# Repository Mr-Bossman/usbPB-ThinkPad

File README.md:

# usbPB-ThinkPad
A usb PD converter for lenovo slim tip chargers

Writen in C, small ram and code space.

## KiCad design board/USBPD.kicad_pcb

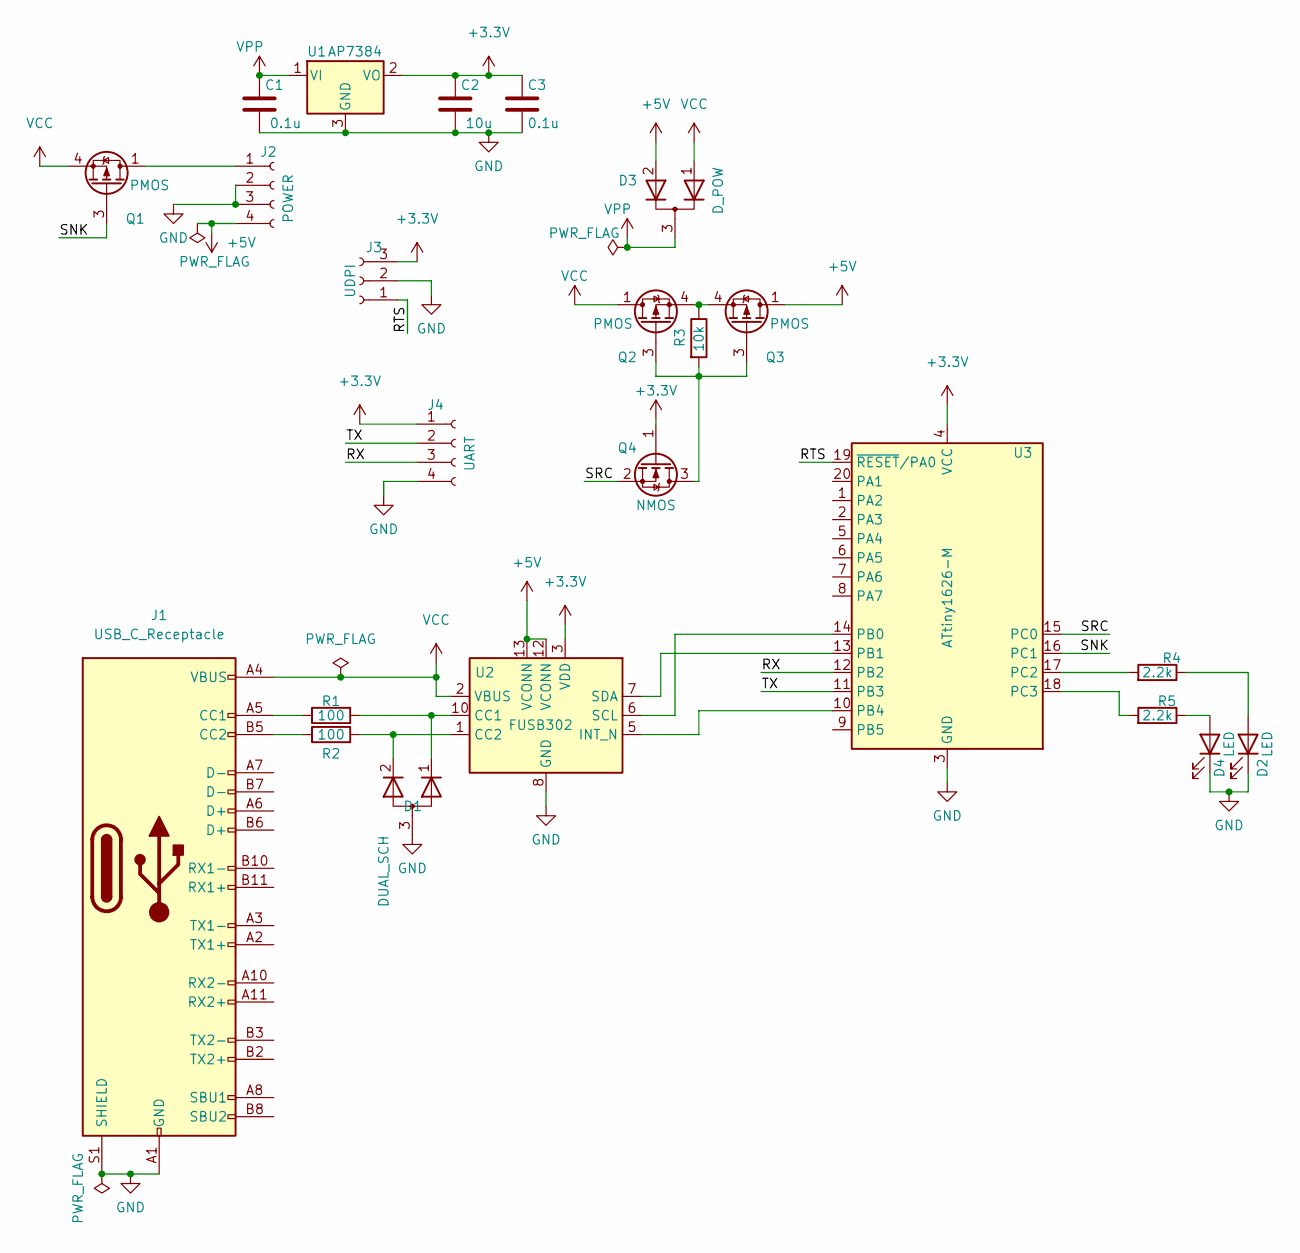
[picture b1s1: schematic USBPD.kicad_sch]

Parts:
C1, C3: 0.1u; C_0603_1608Metric
C2: 10u; C_0603_1608Metric
D1: DUAL_SCH; SOT-23
D2, D4: LED; LED_0603_1608Metric
D3: D_POW; SOT-23
J1: USB_C_Receptacle; USB_C_Receptacle_GCT_USB4085
J2: POWER; PinHeader_1x04_P2.54mm_Vertical
J3: UDPI; SolderJumper-3_P1.3mm_Open_RoundedPad1.0x1.5mm_NumberLabels
J4: UART; Molex_PicoBlade_53047-0410_1x04_P1.25mm_Vertical
Q1, Q2, Q3: PMOS; SOT-23-6
Q4: NMOS; SOT-23
R1, R2: 100; R_0603_1608Metric
R3: 10k; R_0603_1608Metric
R4, R5: 2.2k; R_0603_1608Metric
U1: AP7384; SOT-23
U2: FUSB302; WQFN-14-1EP_2.5x2.5mm_P0.5mm_EP1.45x1.45mm
U3: ATtiny1626-M; VQFN-20-1EP_3x3mm_P0.4mm_EP1.7x1.7mm

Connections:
+3.3V: C2.1, C3.1, J3.3, J4.1, Q4.1 (G), U1.2 (VO), U2.3 (VDD), U2.4 (VDD), U3.4 (VCC)
+5V: D3.2 (K), J2.4, Q3.1 (D), Q3.2 (D), Q3.5 (D), Q3.6 (D), U2.12 (VCONN), U2.13 (VCONN)
/RTS: J3.1, U3.19 (~RESET/PA0)
/RX: J4.3, U3.12 (PB2)
/SNK: Q1.3 (G), U3.16 (PC1)
/SRC: Q4.2 (S), U3.15 (PC0)
/TX: J4.2, U3.11 (PB3)
GND: C1.2, C2.2, C3.2, D1.3 (A), D2.1 (K), D4.1 (K), J1.A1 (GND), J1.A12 (GND), J1.B1 (GND), J1.B12 (GND), J1.S1 (SHIELD), J2.2, J2.3, J3.2, J4.4, U1.3 (GND), U2.8 (GND), U2.9 (GND), U2.15 (GND), U3.3 (GND), U3.21 (GND)
unnamed: D1.1 (K), R1.2, U2.10 (CC1), U2.11 (CC1)
unnamed: D1.2 (K), R2.2, U2.1 (CC2), U2.14 (CC2)
unnamed: D2.2 (A), R4.1
unnamed: D4.2 (A), R5.1
unnamed: J1.A5 (CC1), R1.1
unnamed: J1.B5 (CC2), R2.1
unnamed: J2.1, Q1.1 (D), Q1.2 (D), Q1.5 (D), Q1.6 (D)
unnamed: Q2.3 (G), Q3.3 (G), Q4.3 (D), R3.2
unnamed: Q2.4 (S), Q3.4 (S), R3.1
unnamed: R4.2, U3.17 (PC2)
unnamed: R5.2, U3.18 (PC3)
unnamed: U2.5 (INT_N), U3.10 (PB4)
unnamed: U2.6 (SCL), U3.14 (PB0)
unnamed: U2.7 (SDA), U3.13 (PB1)
VCC: D3.1 (K), J1.A4 (VBUS), J1.A9 (VBUS), J1.B4 (VBUS), J1.B9 (VBUS), Q1.4 (S), Q2.1 (D), Q2.2 (D), Q2.5 (D), Q2.6 (D), U2.2 (VBUS)
VPP: C1.1, D3.3 (A), U1.1 (VI)

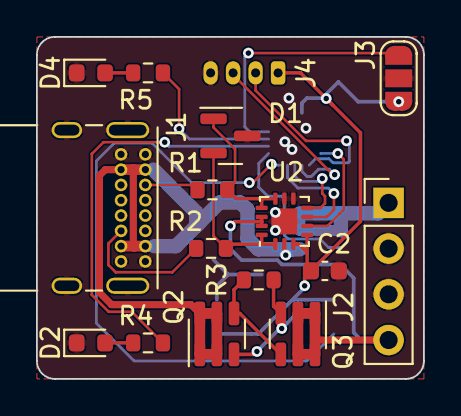
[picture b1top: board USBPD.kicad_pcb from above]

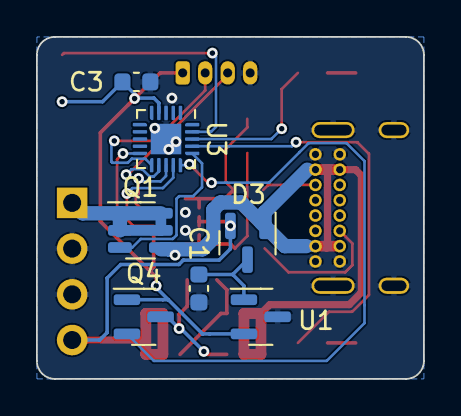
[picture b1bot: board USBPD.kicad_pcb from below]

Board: 2 copper layers, 21.5 x 19.0 mm, 23 parts (7 on the bottom side), 24 nets.

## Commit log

2022-09-03 Init
2022-09-05 i2c works now and started usb302 setup
2022-09-06 more comunication
2022-09-06 gets caps
2022-09-06 uart
2022-09-06 print caps
2022-09-07 watch dog and callback
2022-09-07 needs to set pwr
2022-09-07 can set V
2022-09-07 some formating and small upating
2022-09-07 found a bug
2022-09-08 another bug cant reset b4 detach
2022-09-08 Add readme
2022-09-11 usbPD board init
2022-11-04 move to tn1624
2022-11-04 update pcb
2022-11-05 staring to work on 1624
2022-11-14 usb pd state machine mostly implemented just need reset and err detection now
2022-11-14 should work using 5v and power up
2022-11-15 sink seems to work
2023-01-21 source wont detect detach
2023-01-21 src now detects hot-plug
2023-01-23 works with terminated usbc cables
2023-01-27 use LVL translator for switch
